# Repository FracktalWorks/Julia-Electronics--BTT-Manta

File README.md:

# Julia-Mark-III-Electronics--BTT-Manta
Daughter Board, Chassis Board, Extruder Boards and ABL boards that is based out of BTT Manta boards

HV - High Voltage - 48V

VBB - 24V

Note: The Daughter board already has a jumper installed as per the mappings and the required voltages for the Fan and probe pin voltage selection, an additional set of jumper caps are not required to install.

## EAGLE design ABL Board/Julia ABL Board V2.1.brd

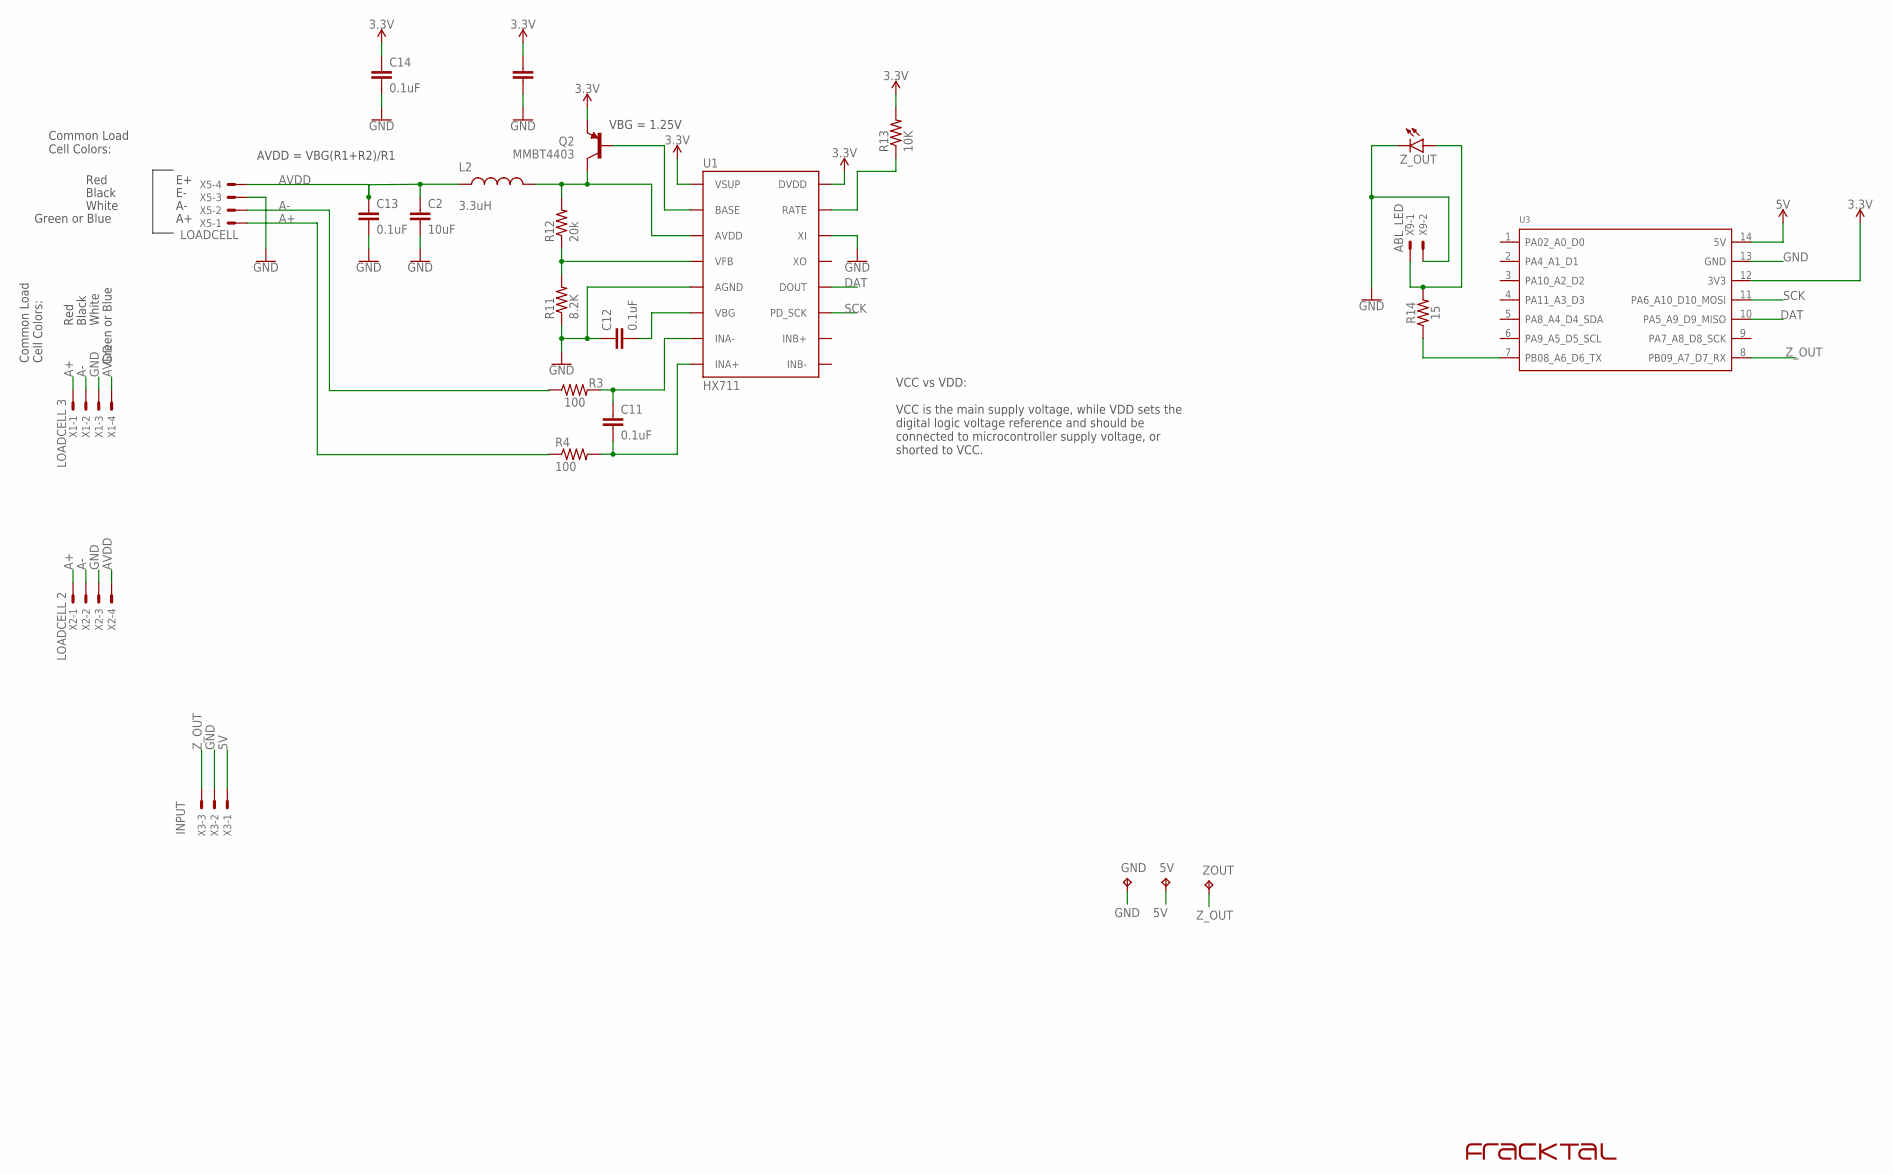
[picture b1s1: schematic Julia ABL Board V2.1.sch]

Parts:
5V: TPB2,54; B2,54
C1, C2: 10uF; 1210
C11, C12, C13, C14: 0.1uF; 0603-CAP
GND: TPB2,54; B2,54
L2: 3.3uH; 0805
Q2: MMBT4403; SOT23-3
R3, R4: 100; 0603-RES
R11: 8.2K; 0603-RES
R12: 20k; 0603-RES
R13: 10K; 0603-RES
R14: 15; 0603
U1: HX711; SO16
U3: MOUDLE-SEEEDUINO-XIAO; MOUDLE14P-2.54-21X17.8MM
U$2: FRACKTALLOGO
X1: LOADCELL 3; JST-XH-04-PACKAGE-LONG-PAD
X2: LOADCELL 2; JST-XH-04-PACKAGE-LONG-PAD
X3: JST-XH-03-PIN-LONG-PAD; JST-XH-03-PACKAGE-LONG-PAD
X5: LOADCELL; JST-XH-04-PACKAGE-LONG-PAD
X9: ABL_LED; JST-XH-02-PACKAGE-LONG-PAD
ZOUT: TPB2,54; B2,54
Z_OUT: LEDSML0603; SML0603

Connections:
3.3V: C1.1, C14.1, Q2.2 (E), R13.2, U1.1 (VSUP), U1.16 (DVDD), U3.12 (3V3)
5V: 5V.TP, U3.14 (5V), X3.1
A+: R4.1, X1.1, X2.1, X5.1
A-: R3.1, X1.2, X2.2, X5.2
AVDD: C2.1, C13.1, L2.1, X1.4, X2.4, X5.4
DAT: U1.12 (DOUT), U3.10 (PA5_A9_D9_MISO)
GND: C1.2, C2.2, C12.1, C13.2, C14.2, GND.TP, R11.1, U1.5 (AGND), U1.14 (XI), U3.13 (GND), X1.3, X2.3, X3.2, X5.3, X9.2, Z_OUT.C
unnamed: Q2.1 (B), U1.2 (BASE)
unnamed: R11.2, R12.1, U1.4 (VFB)
unnamed: C12.2, U1.6 (VBG)
unnamed: L2.2, Q2.3 (C), R12.2, U1.3 (AVDD)
unnamed: R13.1, U1.15 (RATE)
unnamed: C11.1, R3.2, U1.7 (INA-)
unnamed: C11.2, R4.2, U1.8 (INA+)
unnamed: R14.2, X9.1, Z_OUT.A
unnamed: R14.1, U3.7 (PB08_A6_D6_TX)
SCK: U1.11 (PD_SCK), U3.11 (PA6_A10_D10_MOSI)
Z_OUT: U3.8 (PB09_A7_D7_RX), X3.3, ZOUT.TP

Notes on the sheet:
Red
Black
White
Green or Blue
Common Load Cell Colors:
VBG = 1.25V
AVDD = VBG(R1+R2)/R1
VCC vs VDD: VCC is the main supply voltage, while VDD sets the digital logic voltage reference and should be connected to microcontroller supply voltage, or shorted to VCC.

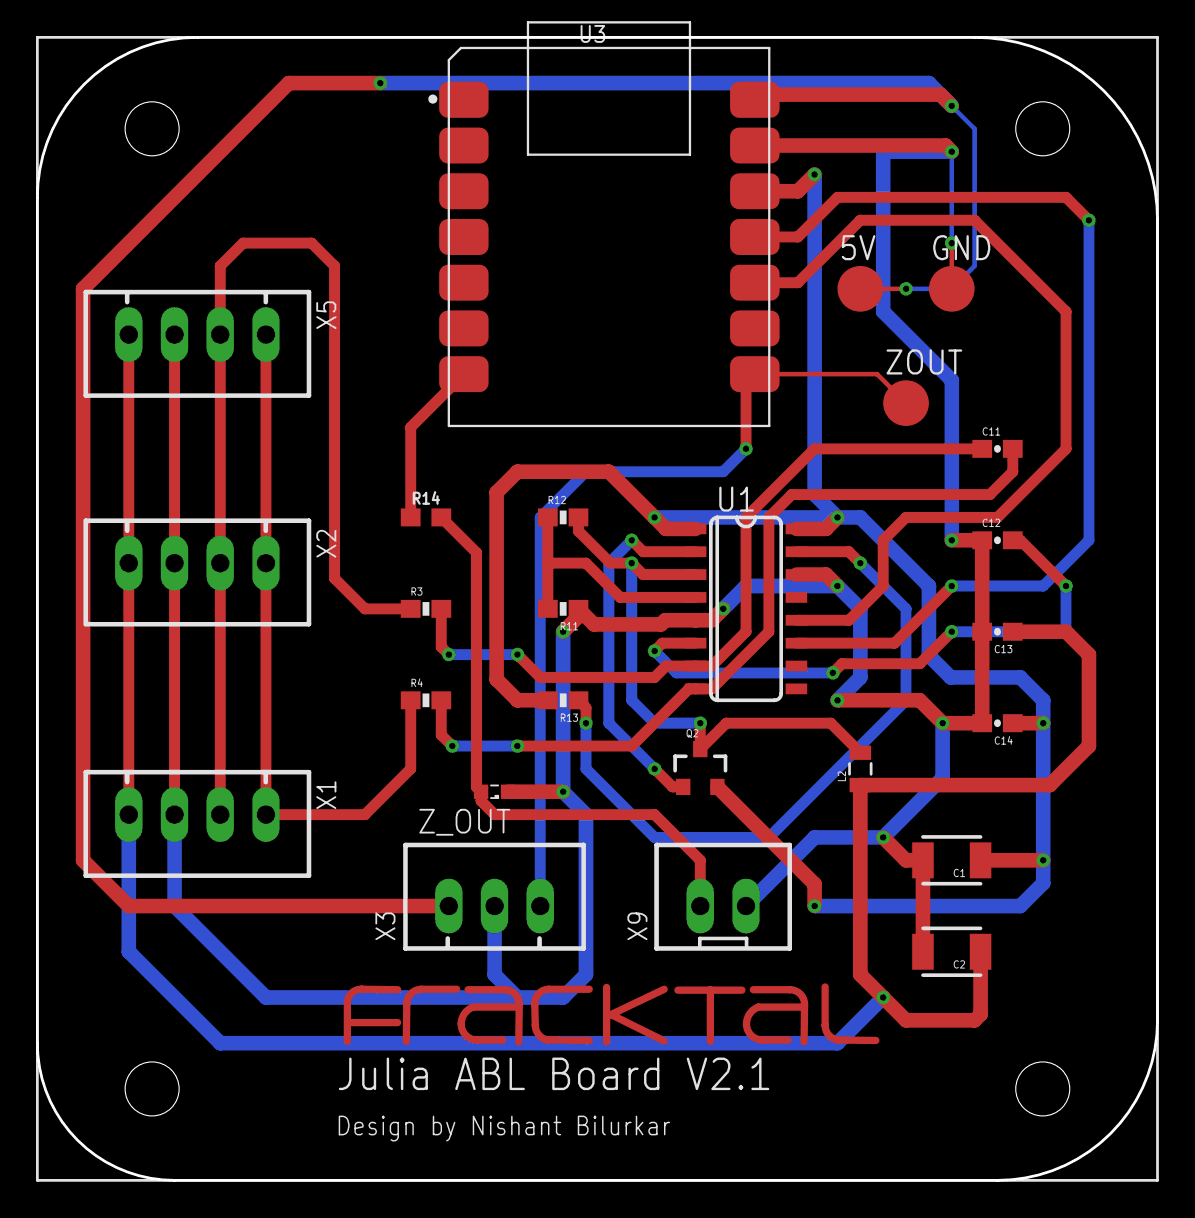
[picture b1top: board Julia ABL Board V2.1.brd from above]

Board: 2 copper layers, 62.2 x 63.5 mm, 26 parts (0 on the bottom side), 18 nets.

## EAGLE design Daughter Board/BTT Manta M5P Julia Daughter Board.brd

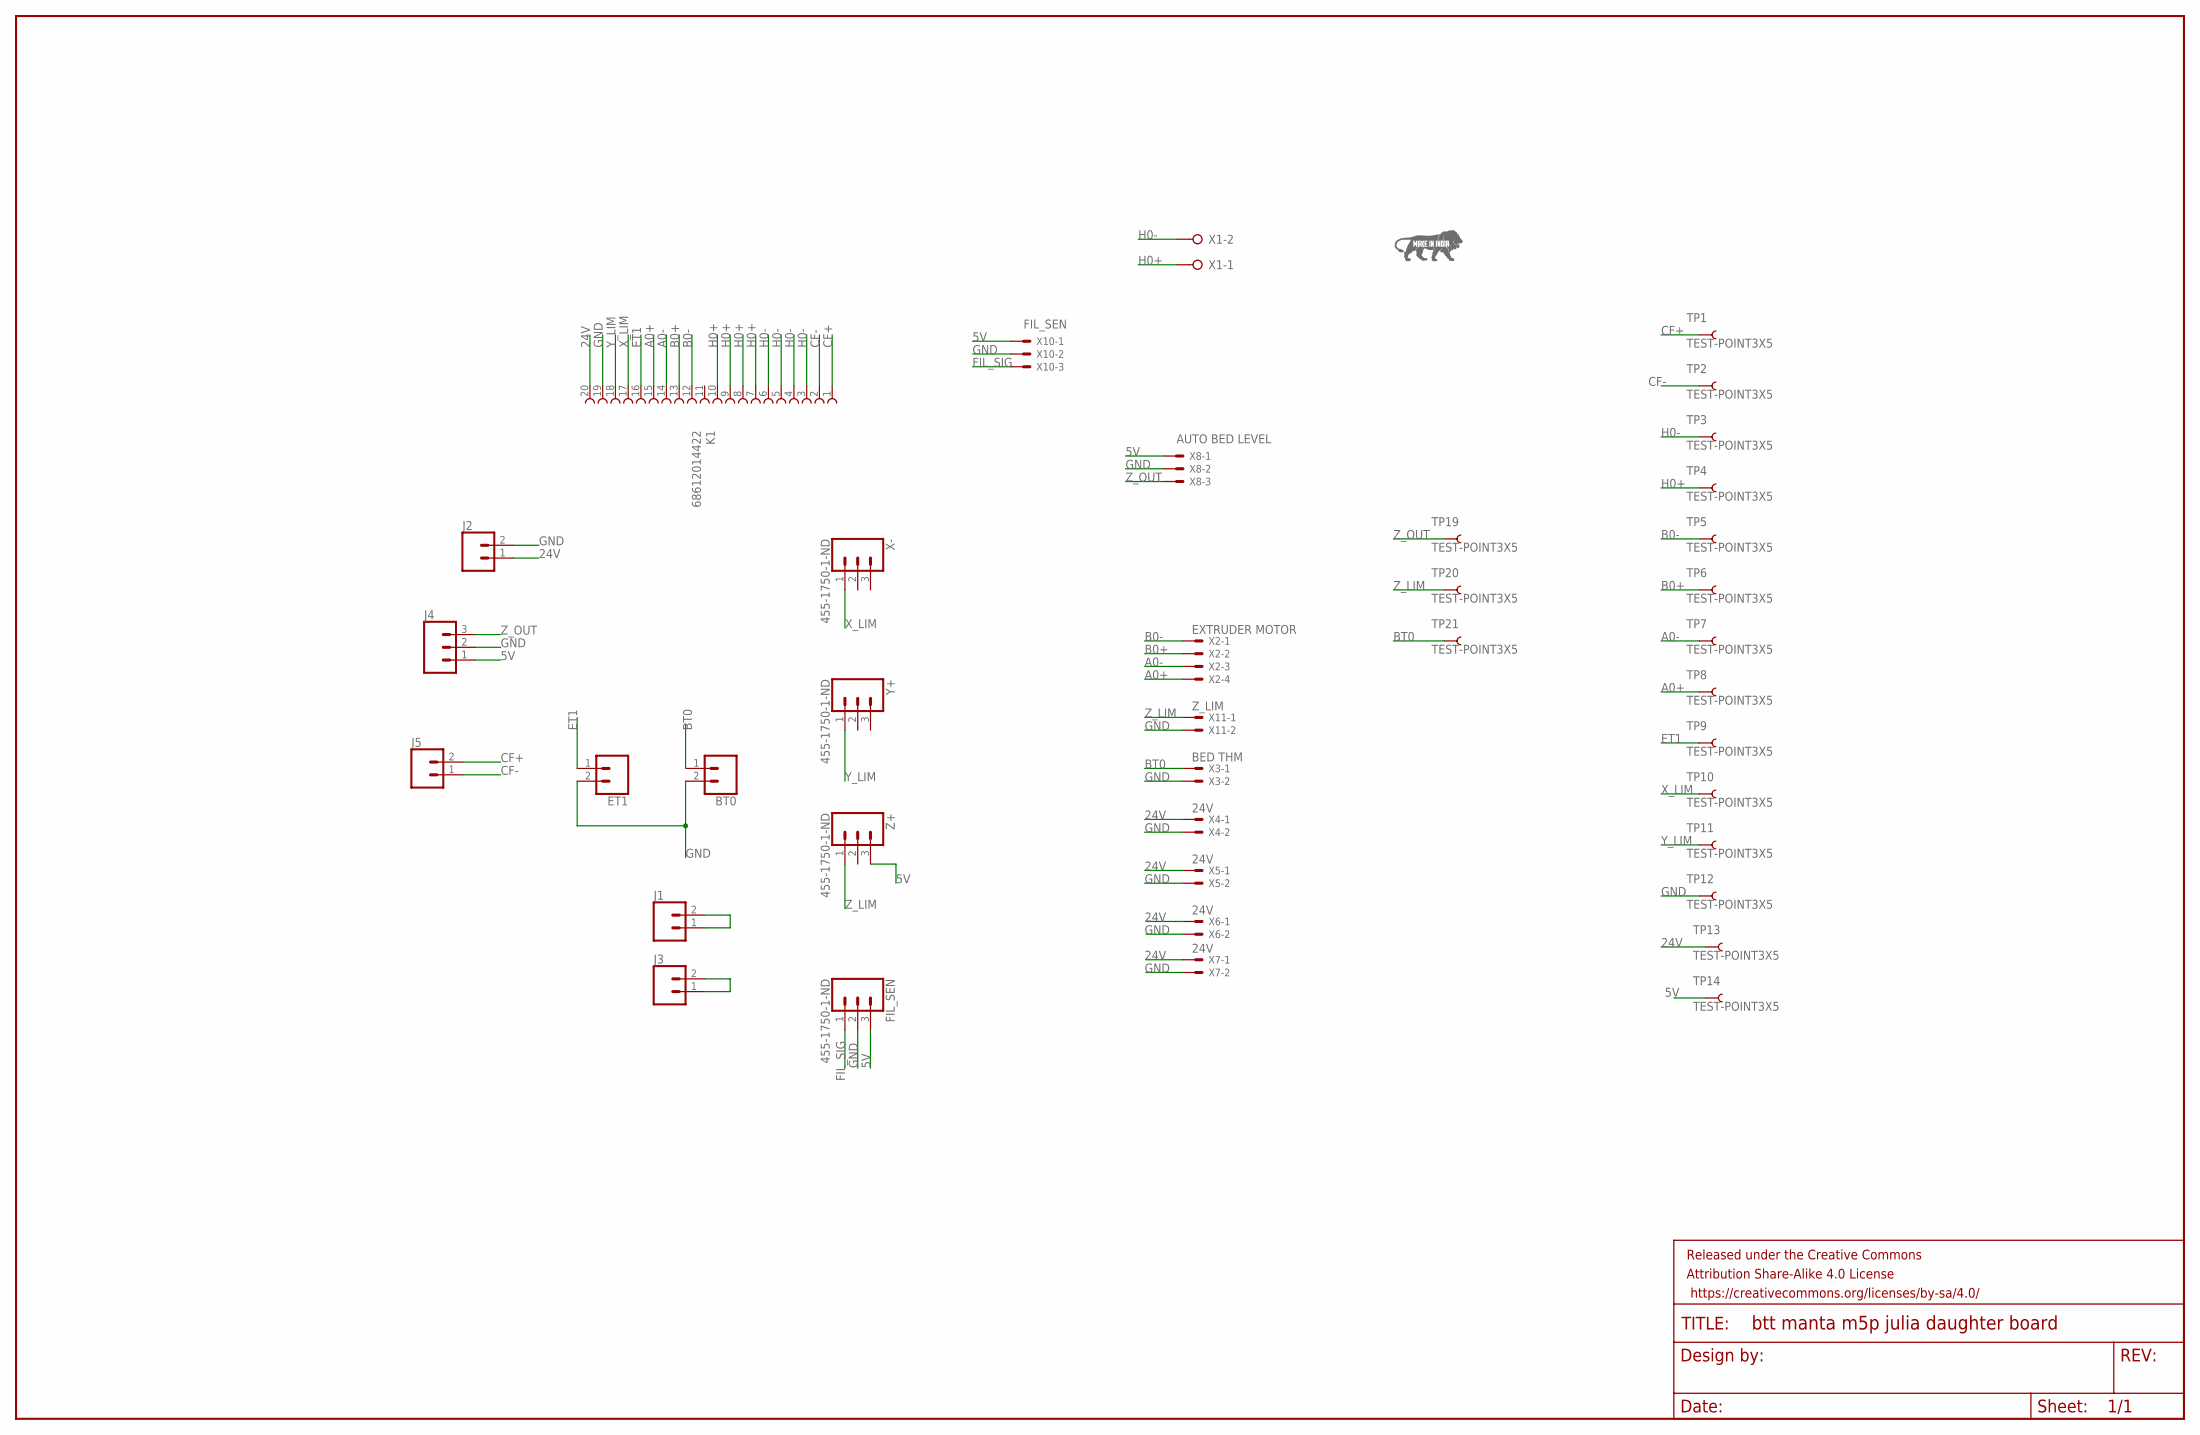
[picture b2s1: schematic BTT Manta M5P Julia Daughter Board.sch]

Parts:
BT0: CONN_02; 1X02
ET1: CONN_02; 1X02
FIL_SEN: 455-1750-1-ND; 1X03
FRAME1: FRAME-LEDGER; CREATIVE_COMMONS
J1, J2, J3, J5: CONN_02; 1X02
J4: CONN_03; 1X03
K1: 68612014422
TP1, TP2, TP3, TP4, TP5, TP6, TP7, TP8, TP9, TP10, TP11, TP12, TP13, TP14, TP19, TP20, TP21: TEST-POINT3X5; PAD.03X.05
U$2: MAKEININDIA
X1: W237-02P; W237-132
X2: EXTRUDER MOTOR; JST-XH-04-PACKAGE-LONG-PAD
X3: BED THM; JST-XH-02-PACKAGE-LONG-PAD
X4, X5, X6, X7: 24V; JST-XH-02-PACKAGE-LONG-PAD
X8, X10: JST-XH-03-PIN-LONG-PAD; JST-XH-03-PACKAGE-LONG-PAD
X11: Z_LIM; JST-XH-02-PACKAGE-LONG-PAD
X-: 455-1750-1-ND; 1X03
Y+: 455-1750-1-ND; 1X03
Z+: 455-1750-1-ND; 1X03

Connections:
5V: FIL_SEN.3, J4.1, TP14.P$1, X8.1, X10.1, Z+.3
24V: J2.1, K1.20, TP13.P$1, X4.1, X5.1, X6.1, X7.1
A0+: K1.15, TP8.P$1, X2.4
A0-: K1.14, TP7.P$1, X2.3
B0+: K1.13, TP6.P$1, X2.2
B0-: K1.12, TP5.P$1, X2.1
BT0: BT0.1, TP21.P$1, X3.1
CF+: J5.2, K1.1, TP1.P$1
CF-: J5.1, K1.2, TP2.P$1
ET1: ET1.1, K1.16, TP9.P$1
FIL_SIG: FIL_SEN.1, X10.3
GND: BT0.2, ET1.2, FIL_SEN.2, J2.2, J4.2, K1.19, TP12.P$1, X3.2, X4.2, X5.2, X6.2, X7.2, X8.2, X10.2, X11.2
H0+: K1.7, K1.8, K1.9, K1.10, TP4.P$1, X1.1
H0-: K1.3, K1.4, K1.5, K1.6, TP3.P$1, X1.2
unnamed: J1.1, J1.2
unnamed: J3.1, J3.2
X_LIM: K1.17, TP10.P$1, X-.1
Y_LIM: K1.18, TP11.P$1, Y+.1
Z_LIM: TP20.P$1, X11.1, Z+.1
Z_OUT: J4.3, TP19.P$1, X8.3

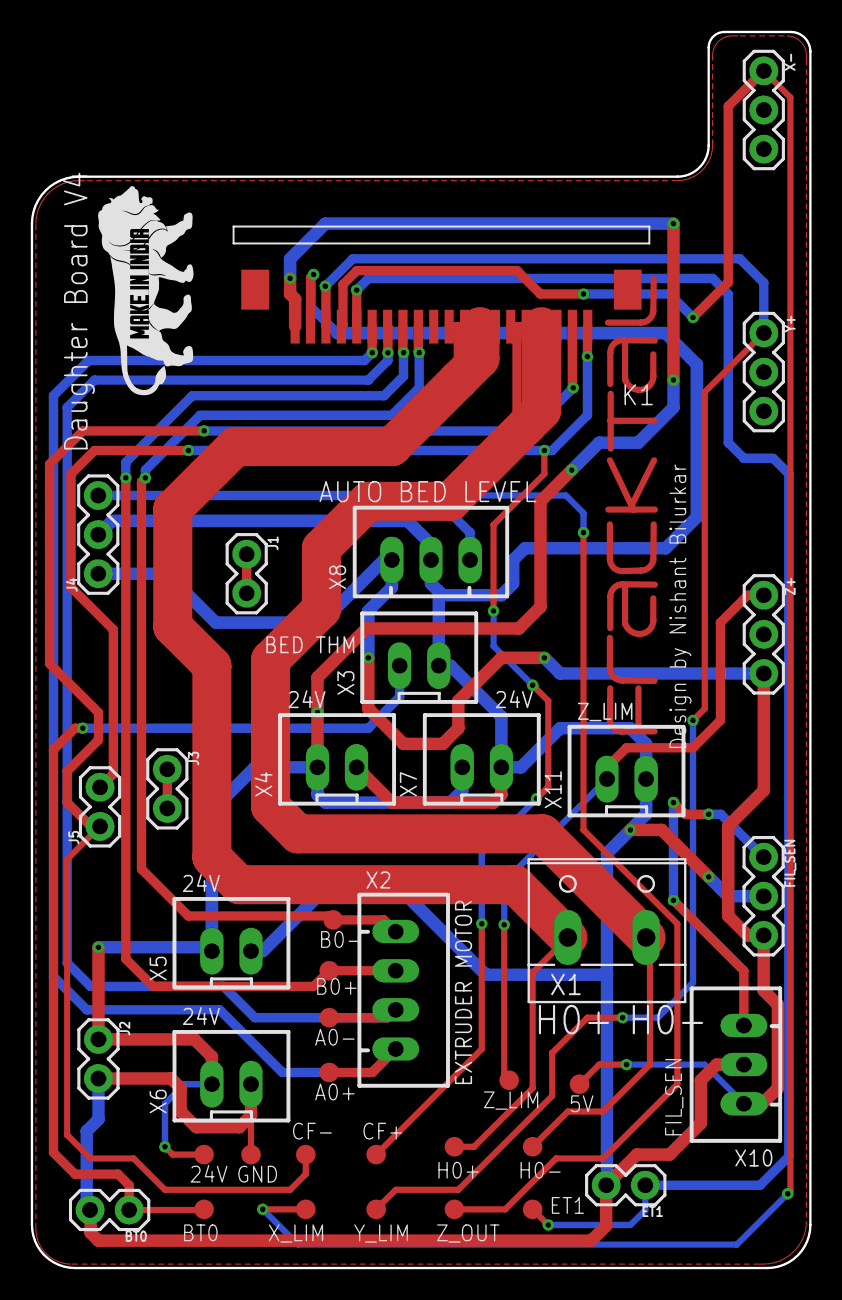
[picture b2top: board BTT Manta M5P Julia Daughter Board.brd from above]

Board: 2 copper layers, 50.5 x 80.3 mm, 42 parts (0 on the bottom side), 20 nets.

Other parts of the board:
U$1: FRACKTALLOGO

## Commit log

2023-07-12 Uploaded Manta M5P .dxf, daughter board .sch and .brd files
2023-07-12 Certain position changes and added fil sensor connectors
2023-07-12 rearranged
2023-07-13 Changed Probe pin voltage to 5V
2023-07-13 Added Julia ABL Board V2.1
2023-07-20 Update README.md
    Added jumper cap installation on motor driver section and voltage selections

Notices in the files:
parts and their libraries:
SparkFun-Capacitors: Licensing: Creative Commons ShareAlike 4.0 International - https://creativecommons.org/licenses/by-sa/4.0
Wurth_Elektronik_Electromechanic_FPC_Con: Copyright: Würth Elektronik
SparkFun-Aesthetics: Released under the Creative Commons Attribution Share-Alike 4.0 License
